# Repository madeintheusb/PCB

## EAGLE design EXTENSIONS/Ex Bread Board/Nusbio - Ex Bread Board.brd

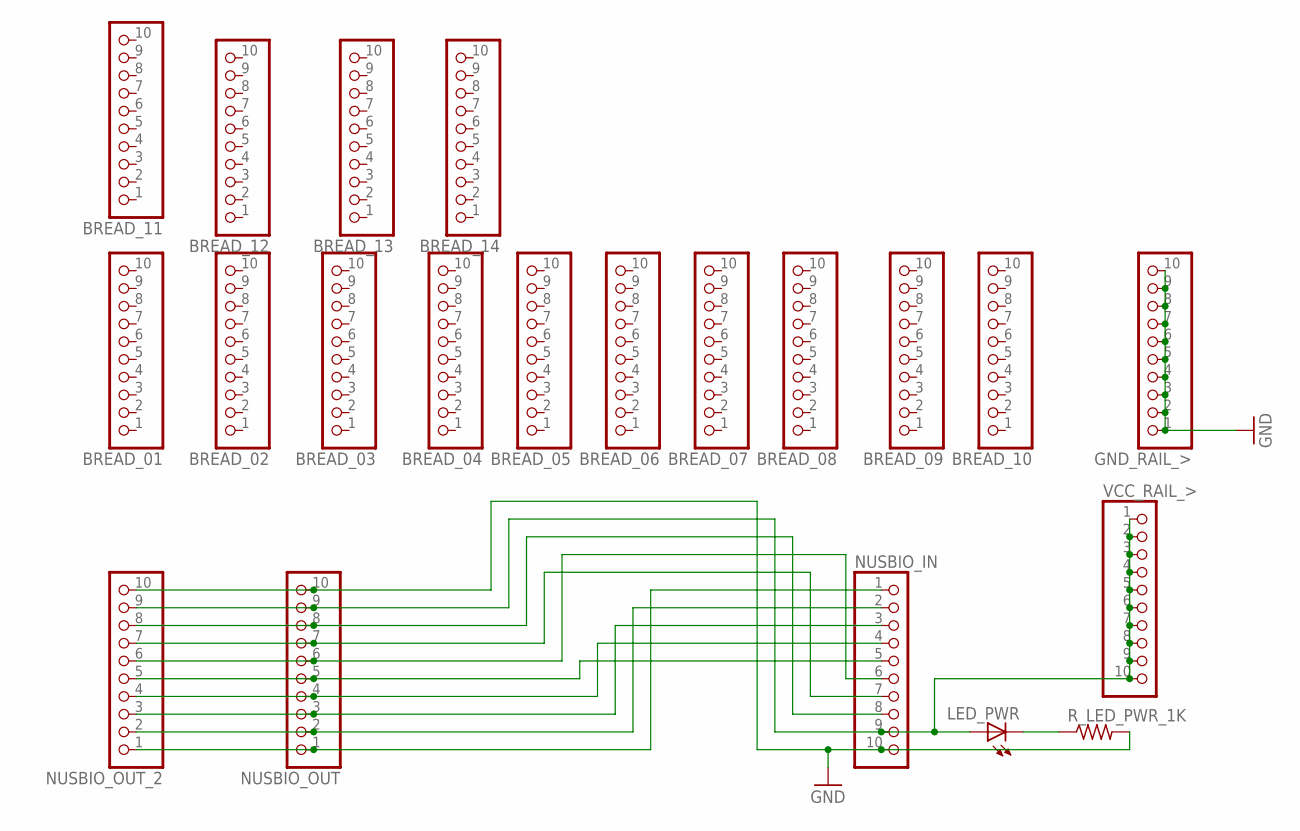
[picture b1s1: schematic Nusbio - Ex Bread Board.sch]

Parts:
BREAD_01, BREAD_02, BREAD_03, BREAD_04, BREAD_05, BREAD_06, BREAD_07, BREAD_08, BREAD_09, BREAD_10, BREAD_11, BREAD_12, BREAD_13, BREAD_14: PINHD-1X10; 1X10-BIG
GND_RAIL_>: PINHD-1X10; 1X10-BIG
LED_PWR: LEDSMT1206; 1206
NUSBIO_IN: PINHD-1X10; 1X10-BIG
NUSBIO_OUT: PINHD-1X10; 1X10-BIG
NUSBIO_OUT_2: PINHD-1X10; 1X10-BIG
R_LED_PWR_1K: R-US_R1206; R1206
VCC_RAIL_>: PINHD-1X10; 1X10-BIG

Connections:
GND: GND_RAIL_>.1, GND_RAIL_>.2, GND_RAIL_>.3, GND_RAIL_>.4, GND_RAIL_>.5, GND_RAIL_>.6, GND_RAIL_>.7, GND_RAIL_>.8, GND_RAIL_>.9, GND_RAIL_>.10, NUSBIO_IN.10, NUSBIO_OUT.10, NUSBIO_OUT_2.10, R_LED_PWR_1K.2
unnamed: NUSBIO_IN.1, NUSBIO_OUT.1, NUSBIO_OUT_2.1
unnamed: NUSBIO_IN.2, NUSBIO_OUT.2, NUSBIO_OUT_2.2
unnamed: NUSBIO_IN.3, NUSBIO_OUT.3, NUSBIO_OUT_2.3
unnamed: NUSBIO_IN.4, NUSBIO_OUT.4, NUSBIO_OUT_2.4
unnamed: NUSBIO_IN.5, NUSBIO_OUT.5, NUSBIO_OUT_2.5
unnamed: NUSBIO_IN.6, NUSBIO_OUT.6, NUSBIO_OUT_2.6
unnamed: NUSBIO_IN.7, NUSBIO_OUT.7, NUSBIO_OUT_2.7
unnamed: NUSBIO_IN.8, NUSBIO_OUT.8, NUSBIO_OUT_2.8
unnamed: LED_PWR.A, NUSBIO_IN.9, NUSBIO_OUT.9, NUSBIO_OUT_2.9, VCC_RAIL_>.1, VCC_RAIL_>.2, VCC_RAIL_>.3, VCC_RAIL_>.4, VCC_RAIL_>.5, VCC_RAIL_>.6, VCC_RAIL_>.7, VCC_RAIL_>.8, VCC_RAIL_>.9, VCC_RAIL_>.10
unnamed: LED_PWR.C, R_LED_PWR_1K.1

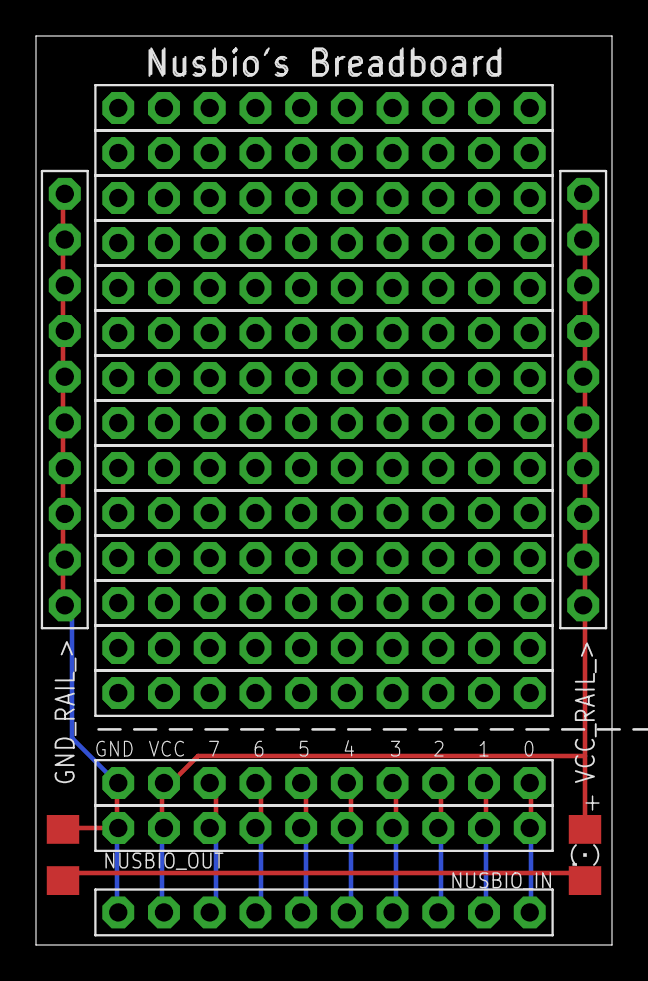
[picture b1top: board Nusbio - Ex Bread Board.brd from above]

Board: 2 copper layers, 32.0 x 50.5 mm, 21 parts (0 on the bottom side), 11 nets.

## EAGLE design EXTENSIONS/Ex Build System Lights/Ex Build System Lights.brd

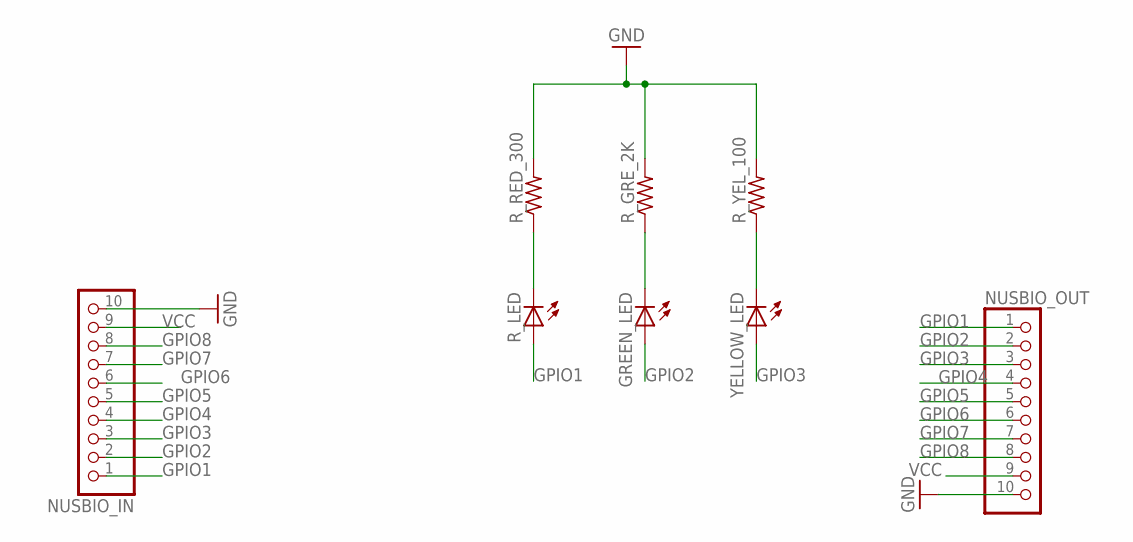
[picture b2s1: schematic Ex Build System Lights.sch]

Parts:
GREEN_LED: LED5MM
NUSBIO_IN: PINHD-1X10; 1X10-BIG
NUSBIO_OUT: PINHD-1X10; 1X10-BIG
R_GRE_2K: R-US_R1206; R1206
R_LED: LED5MM
R_RED_300: R-US_R1206; R1206
R_YEL_100: R-US_R1206; R1206
YELLOW_LED: LED5MM

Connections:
GND: NUSBIO_IN.10, NUSBIO_OUT.10, R_GRE_2K.2, R_RED_300.2, R_YEL_100.2
GPIO1: NUSBIO_IN.1, NUSBIO_OUT.1, R_LED.A
GPIO2: GREEN_LED.A, NUSBIO_IN.2, NUSBIO_OUT.2
GPIO3: NUSBIO_IN.3, NUSBIO_OUT.3, YELLOW_LED.A
GPIO4: NUSBIO_IN.4, NUSBIO_OUT.4
GPIO5: NUSBIO_IN.5, NUSBIO_OUT.5
GPIO6: NUSBIO_IN.6, NUSBIO_OUT.6
GPIO7: NUSBIO_IN.7, NUSBIO_OUT.7
GPIO8: NUSBIO_IN.8, NUSBIO_OUT.8
unnamed: R_LED.K (C), R_RED_300.1
unnamed: GREEN_LED.K (C), R_GRE_2K.1
unnamed: R_YEL_100.1, YELLOW_LED.K (C)
VCC: NUSBIO_IN.9, NUSBIO_OUT.9

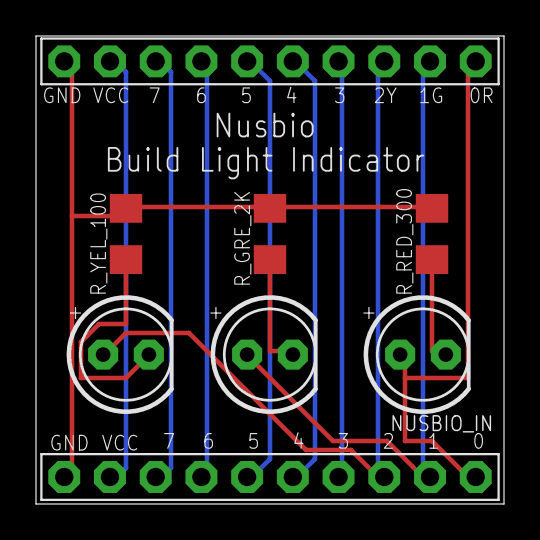
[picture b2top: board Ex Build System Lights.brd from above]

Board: 2 copper layers, 26.0 x 26.0 mm, 8 parts (0 on the bottom side), 13 nets.

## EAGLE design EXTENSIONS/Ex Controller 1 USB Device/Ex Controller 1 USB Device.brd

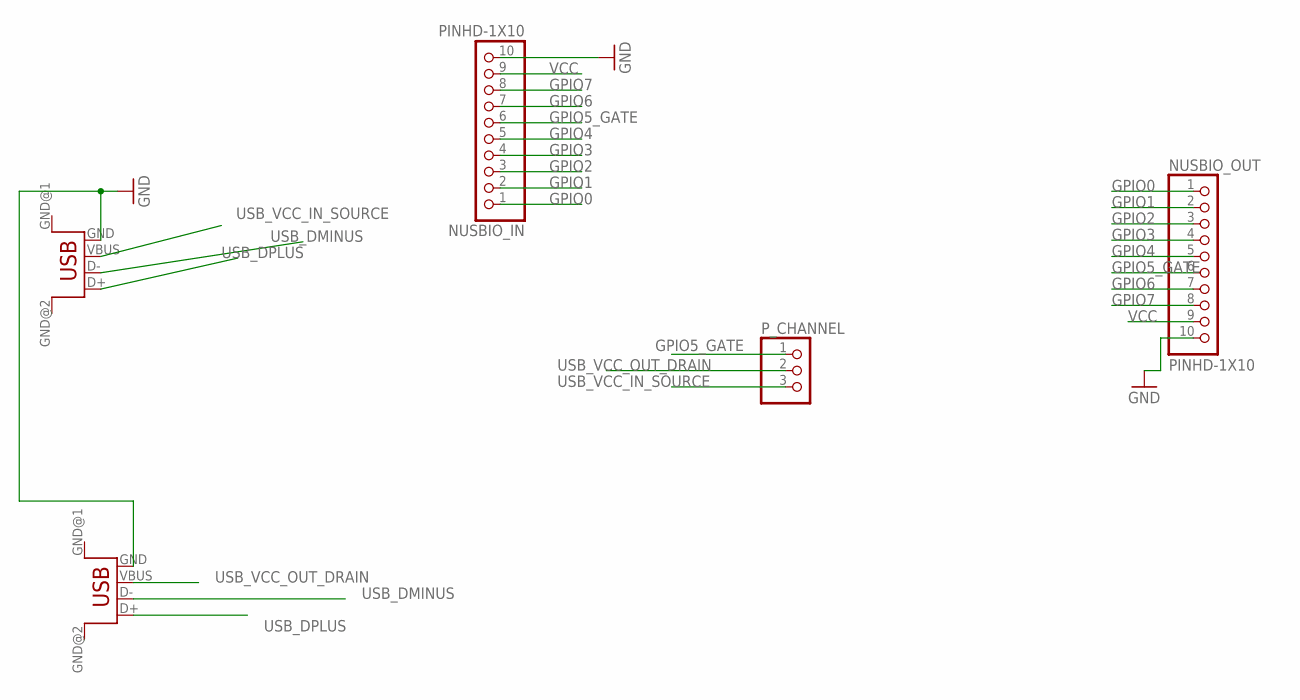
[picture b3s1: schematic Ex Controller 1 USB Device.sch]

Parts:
NUSBIO_IN: PINHD-1X10; 1X10-BIG
NUSBIO_OUT: PINHD-1X10; 1X10-BIG
P_CHANNEL: PINHD-1X3; 1X03
USB_DEV_INPUT: USB; USB-FEMALE-A-PTH
USB_DEV_OUTPUT: USB; USB-FEMALE-A-PTH

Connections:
GND: NUSBIO_IN.10, NUSBIO_OUT.10, USB_DEV_INPUT.GND, USB_DEV_OUTPUT.GND
GPIO0: NUSBIO_IN.1, NUSBIO_OUT.1
GPIO1: NUSBIO_IN.2, NUSBIO_OUT.2
GPIO2: NUSBIO_IN.3, NUSBIO_OUT.3
GPIO3: NUSBIO_IN.4, NUSBIO_OUT.4
GPIO4: NUSBIO_IN.5, NUSBIO_OUT.5
GPIO5_GATE: NUSBIO_IN.6, NUSBIO_OUT.6, P_CHANNEL.1
GPIO6: NUSBIO_IN.7, NUSBIO_OUT.7
GPIO7: NUSBIO_IN.8, NUSBIO_OUT.8
USB_DMINUS: USB_DEV_INPUT.D-, USB_DEV_OUTPUT.D-
USB_DPLUS: USB_DEV_INPUT.D+, USB_DEV_OUTPUT.D+
USB_VCC_IN_SOURCE: P_CHANNEL.3, USB_DEV_INPUT.VBUS
USB_VCC_OUT_DRAIN: P_CHANNEL.2, USB_DEV_OUTPUT.VBUS
VCC: NUSBIO_IN.9, NUSBIO_OUT.9

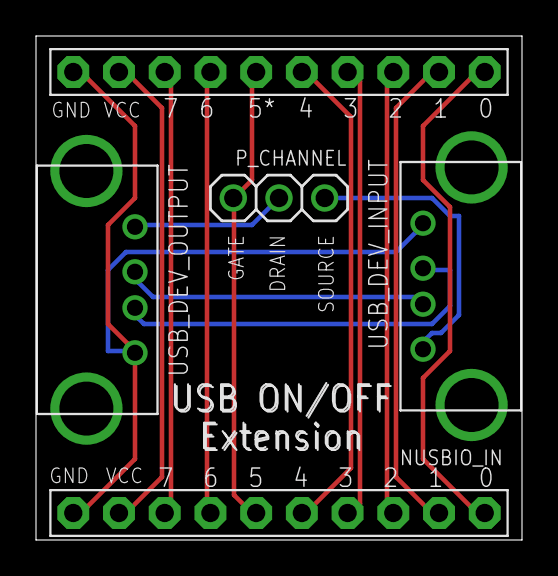
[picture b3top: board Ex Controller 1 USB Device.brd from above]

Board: 2 copper layers, 27.0 x 28.0 mm, 5 parts (0 on the bottom side), 14 nets.
